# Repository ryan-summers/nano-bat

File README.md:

# NanoBat

This repository contains the hardware and software behind NanoBat, a low-cost tool designed for
engineers and hobbyists to simulate batteries in low-power designs.

## Goals
Develop an open-source PCB design and firmware solution for simulating batteries for low-power
designs with a final cost of less than $100 per unit and can accurately simulate battery capacity
over a 24 hour window with **TBD** accuracy.

## Tools
The firmware will be developed in Rust.

The PCB design will be conducted with Kicad.

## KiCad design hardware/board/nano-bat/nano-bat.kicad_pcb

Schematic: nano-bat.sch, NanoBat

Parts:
C101: 10n; C_0603_1608Metric; Part 399-7842-1-ND
C102: 0.1u; C_0603_1608Metric; Part 1276-1258-1-ND
D102: LED; LED_0805_2012Metric; Part 160-1423-1-ND
F101, F102: Polyfuse; Fuse_1812_4532Metric; Part 507-1763-1-ND
FB103: Ferrite_Bead_Small; R_0603_1608Metric; Part 587-1923-1-ND
H101, H102, H103, H104: e; MountingHole_2.2mm_M2_Pad
J101: Barrel_Jack_Switch; CUI_PJ-202B; Part CP-202B-ND
J102: USB_C_Receptacle_USB2.0; USB_C_Receptacle_GCT_USB4085; Part 2073-USB4085-GF-ACT-ND
J103: Screw_Terminal_01x02; TerminalBlock_Phoenix_PT-1,5-2-3.5-H_1x02_P3.50mm_Horizontal; Part 277-1721-ND
J104: Conn_01x02; JST_PH_S2B-PH-SM4-TB_1x02-1MP_P2.00mm_Horizontal; Part 455-1749-1-ND
Q101, Q102: Q_PMOS_GSD; SOT-23; Part FDN352APCT-ND
R101, R102: 1M; R_0603_1608Metric; Part 311-1.00MHRCT-ND
R103: 1k; R_0603_1608Metric; Part 311-1.0KGRCT-ND
R104, R105: 5.1k; R_0603_1608Metric; Part RMCF0603JT5K10CT-ND
U101: USBLC6-2SC6; SOT-23-6; Part 497-5235-1-ND

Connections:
+5V: FB103.2, Q102.3 (D)
/Coulomb Counter/Vbatt_out: J103.1, J104.1; also elsewhere on the board
/Power/Vin: Q101.2 (S), Q102.2 (S), R102.1, R103.1; also elsewhere on the board
/USB_N: U101.6; also elsewhere on the board
/USB_P: U101.4; also elsewhere on the board
GND: C101.2, C102.2, D102.1 (K), H101.1, H102.1, H103.1, H104.1, J101.2, J102.A1, J102.A12, J102.B1, J102.B12, J103.2, J104.2, Q101.1 (G), R101.2, R104.2, R105.2, U101.2; also elsewhere on the board
unnamed: C101.1, J102.S1, R101.1
unnamed: C102.1, F102.2, J102.A4, J102.A9, J102.B4, J102.B9, U101.5
unnamed: D102.2 (A), R103.2
unnamed: F101.1, Q101.3 (D)
unnamed: F101.2, J101.1
unnamed: F102.1, FB103.1
unnamed: J101.3, Q102.1 (G), R102.2
unnamed: J102.A5, R104.1
unnamed: J102.A6, J102.B6, U101.3
unnamed: J102.A7, J102.B7, U101.1
unnamed: J102.B5, R105.1

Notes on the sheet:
When the barrel jack is powered, it will override USB as the supply source and will be used as the main system rail. If the barrel-jack is not connected, USB power will be used.

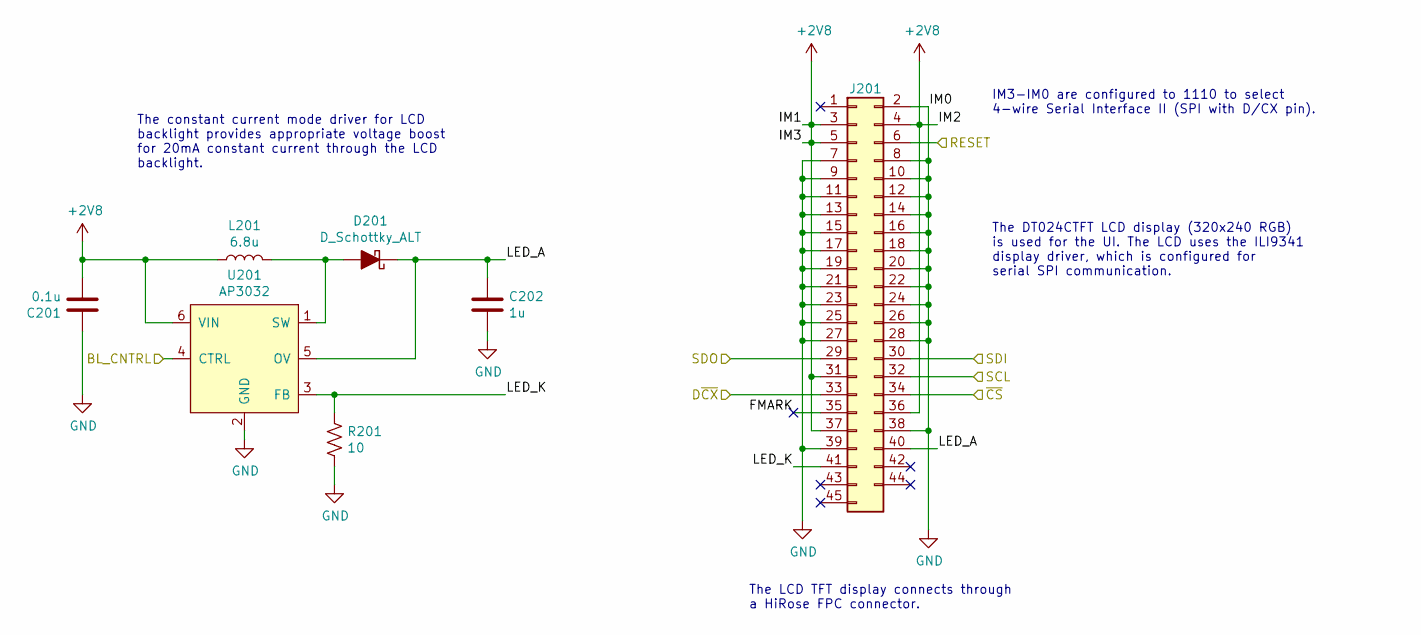
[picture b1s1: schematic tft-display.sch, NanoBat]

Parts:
C201: 0.1u; C_0603_1608Metric; Part 1276-1258-1-ND
C202: 1u; C_0603_1608Metric; Part 1276-1182-1-ND
D201: D_Schottky_ALT; D_SOD-323; Part BAT54HT1GOSCT-ND
J201: Conn_2Rows-45Pins; Hirose_FH12-45S-0.5SH_1x45-1MP_P0.50mm_Horizontal; Part HFA145CT-ND
L201: 6.8u; L_0805_2012Metric; Part 445-6761-1-ND
R201: 10; R_0603_1608Metric; Part 311-10.0HRCT-ND
U201: AP3032; SOT-23-6; Part AP3032KTR-G1DICT-ND

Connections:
+2V8: C201.2, J201.3, J201.4, J201.5, J201.31, J201.36, J201.37, L201.1, U201.6 (VIN); also elsewhere on the board
/(Opt) TFT Display/BL_CNTRL: U201.4 (CTRL); also elsewhere on the board
/(Opt) TFT Display/D~CX: J201.33; also elsewhere on the board
/(Opt) TFT Display/FMARK: J201.35
/(Opt) TFT Display/LED_A: C202.1, D201.1 (K), J201.40, U201.5 (OV)
/(Opt) TFT Display/LED_K: J201.41, R201.1, U201.3 (FB)
/(Opt) TFT Display/RESET: J201.6; also elsewhere on the board
/(Opt) TFT Display/SCL: J201.32; also elsewhere on the board
/(Opt) TFT Display/SDI: J201.30; also elsewhere on the board
/(Opt) TFT Display/SDO: J201.29; also elsewhere on the board
/Microcontroller/TFT_~CS: J201.34; also elsewhere on the board
GND: C201.1, C202.2, J201.2, J201.7, J201.8, J201.9, J201.10, J201.11, J201.12, J201.13, J201.14, J201.15, J201.16, J201.17, J201.18, J201.19, J201.20, J201.21, J201.22, J201.23, J201.24, J201.25, J201.26, J201.27, J201.28, J201.38, J201.39, R201.2, U201.2 (GND); also elsewhere on the board
unnamed: D201.2 (A), L201.2, U201.1 (SW)

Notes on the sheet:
The constant current mode driver for LCD backlight provides appropriate voltage boost for 20mA constant current through the LCD backlight.
The LCD TFT display connects through a HiRose FPC connector.
The DT024CTFT LCD display (320x240 RGB) is used for the UI. The LCD uses the ILI9341 display driver, which is configured for serial SPI communication.
IM3-IM0 are configured to 1110 to select 4-wire Serial Interface II (SPI with D/CX pin).

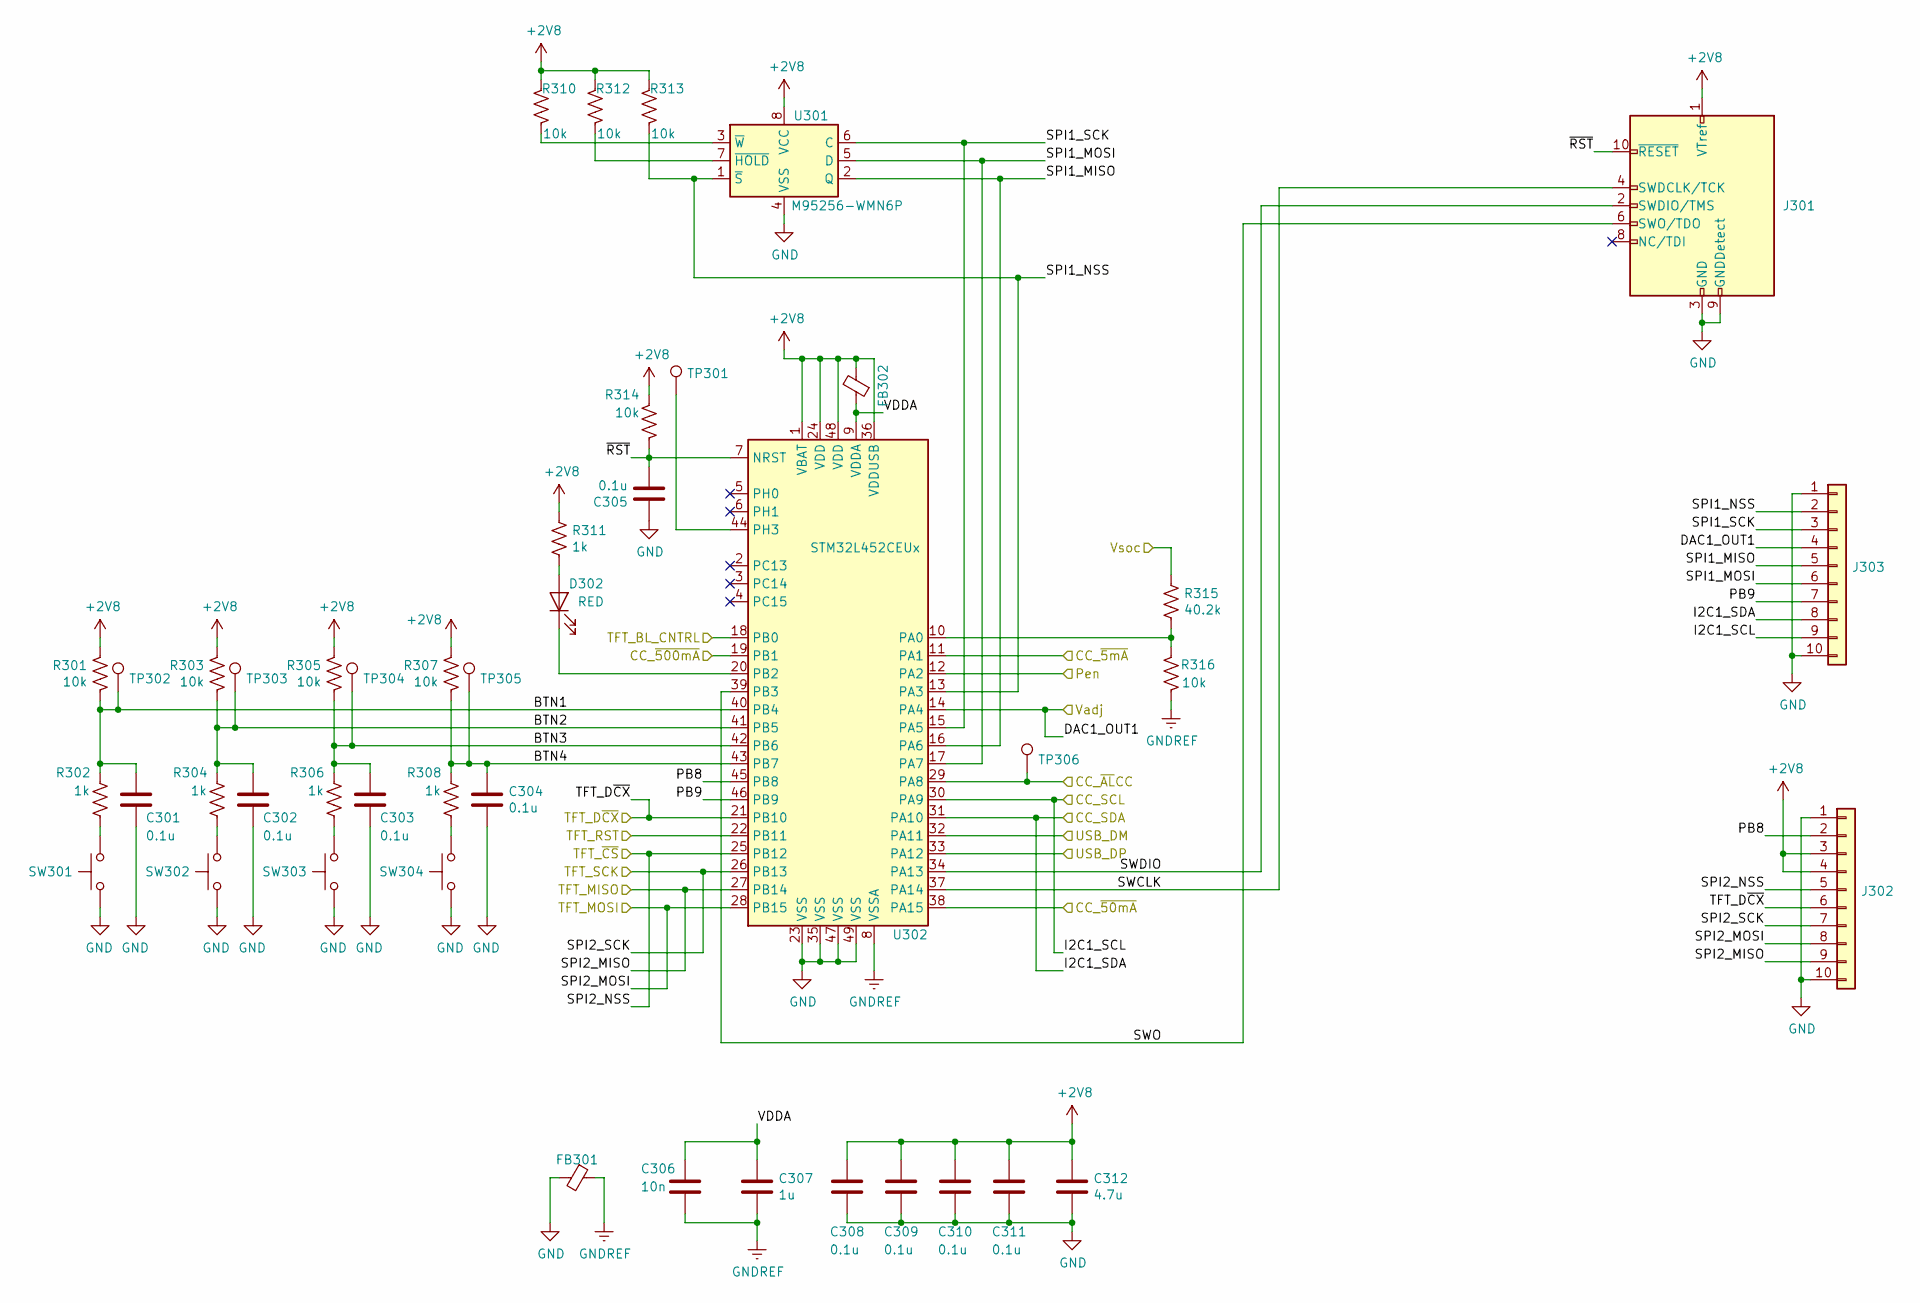
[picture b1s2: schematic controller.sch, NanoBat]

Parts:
C301, C302, C303, C304, C305, C308, C309, C310, C311: 0.1u; C_0603_1608Metric; Part 1276-1258-1-ND
C306: 10n; C_0603_1608Metric; Part 399-7842-1-ND
C307: 1u; C_0603_1608Metric; Part 1276-1182-1-ND
C312: 4.7u; C_0603_1608Metric; Part 399-3482-1-ND
D302: RED; LED_0805_2012Metric; Part 475-1278-1-ND
FB301, FB302: Ferrite_Bead_Small; R_0603_1608Metric; Part 587-1923-1-ND
J301: Conn_ARM_JTAG_SWD_10; PinHeader_2x05_P1.27mm_Vertical_SMD; Part SAM8796-ND
J302, J303: Conn_01x10; PinHeader_1x10_P2.54mm_Vertical; Part 609-3301-ND
R301, R303, R305, R307, R310, R312, R313, R314, R316: 10k; R_0603_1608Metric; Part 311-10KGRCT-ND
R302, R304, R306, R308, R311: 1k; R_0603_1608Metric; Part 311-1.0KGRCT-ND
R315: 40.2k; R_0603_1608Metric; Part RR08P40.2KDCT-ND
SW301, SW302, SW303, SW304: SW_Push; SW_B3FS-1010P; Part SW1440CT-ND
TP301: TestPoint; TestPoint_THTPad_D1.0mm_Drill0.5mm
TP302, TP303, TP304, TP305, TP306: TestPoint; TestPoint_Pad_D1.0mm
U301: M95256-WMN6P; SOIC-8_3.9x4.9mm_P1.27mm; Part 497-6357-5-ND
U302: STM32L452CEUx; QFN-48-1EP_7x7mm_P0.5mm_EP5.6x5.6mm; Part 497-17218-ND

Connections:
+2V8: C308.1, C309.1, C310.1, C311.1, C312.1, FB302.2, J301.1 (VTref), J302.3, J302.4, R301.1, R303.1, R305.1, R307.1, R310.1, R311.1, R312.1, R313.1, R314.1, U301.8 (VCC), U302.1 (VBAT), U302.24 (VDD), U302.36 (VDDUSB), U302.48 (VDD); also elsewhere on the board
/(Opt) TFT Display/BL_CNTRL: U302.18 (PB0); also elsewhere on the board
/(Opt) TFT Display/D~CX: J302.6, U302.21 (PB10); also elsewhere on the board
/(Opt) TFT Display/RESET: U302.22 (PB11); also elsewhere on the board
/(Opt) TFT Display/SCL: J302.7, U302.26 (PB13); also elsewhere on the board
/(Opt) TFT Display/SDI: J302.8, U302.28 (PB15); also elsewhere on the board
/(Opt) TFT Display/SDO: J302.9, U302.27 (PB14); also elsewhere on the board
/Coulomb Counter/Vbatt_source: R315.1; also elsewhere on the board
/Microcontroller/BTN1: C301.1, R301.2, R302.1, TP302.1, U302.40 (PB4)
/Microcontroller/BTN2: C302.1, R303.2, R304.1, TP303.1, U302.41 (PB5)
/Microcontroller/BTN3: C303.1, R305.2, R306.1, TP304.1, U302.42 (PB6)
/Microcontroller/BTN4: C304.1, R307.2, R308.1, TP305.1, U302.43 (PB7)
/Microcontroller/CC_SCL: J303.9, U302.30 (PA9); also elsewhere on the board
/Microcontroller/CC_SDA: J303.8, U302.31 (PA10); also elsewhere on the board
/Microcontroller/CC_~5mA: U302.11 (PA1); also elsewhere on the board
/Microcontroller/CC_~50mA: U302.38 (PA15); also elsewhere on the board
/Microcontroller/CC_~500mA: U302.19 (PB1); also elsewhere on the board
/Microcontroller/CC_~AL~CC: TP306.1, U302.29 (PA8); also elsewhere on the board
/Microcontroller/PB8: J302.2, U302.45 (PB8)
/Microcontroller/PB9: J303.7, U302.46 (PB9)
/Microcontroller/SPI1_MISO: J303.5, U301.2 (Q), U302.16 (PA6)
/Microcontroller/SPI1_MOSI: J303.6, U301.5 (D), U302.17 (PA7)
/Microcontroller/SPI1_NSS: J303.2, R313.2, U301.1 (~S), U302.13 (PA3)
/Microcontroller/SPI1_SCK: J303.3, U301.6 (C), U302.15 (PA5)
/Microcontroller/SWCLK: J301.4 (SWDCLK/TCK), U302.37 (PA14)
/Microcontroller/SWDIO: J301.2 (SWDIO/TMS), U302.34 (PA13)
/Microcontroller/SWO: J301.6 (SWO/TDO), U302.39 (PB3)
/Microcontroller/TFT_~CS: J302.5, U302.25 (PB12); also elsewhere on the board
/Microcontroller/VDDA: C306.1, C307.1, FB302.1, U302.9 (VDDA)
/Microcontroller/Vadj: J303.4, U302.14 (PA4); also elsewhere on the board
/Microcontroller/~RST: C305.2, J301.10 (~RESET~), R314.2, U302.7 (NRST)
/Power/En: U302.12 (PA2); also elsewhere on the board
/USB_N: U302.32 (PA11); also elsewhere on the board
/USB_P: U302.33 (PA12); also elsewhere on the board
GND: C301.2, C302.2, C303.2, C304.2, C305.1, C308.2, C309.2, C310.2, C311.2, C312.2, FB301.2, J301.3 (GND), J301.5 (GND), J301.9 (GNDDetect), J302.1, J302.10, J303.1, J303.10, SW301.2, SW302.2, SW303.2, SW304.2, U301.4 (VSS), U302.23 (VSS), U302.35 (VSS), U302.47 (VSS), U302.49 (VSS); also elsewhere on the board
GNDREF: C306.2, C307.2, FB301.1, R316.2, U302.8 (VSSA)
unnamed: D302.1 (K), U302.20 (PB2)
unnamed: D302.2 (A), R311.2
unnamed: R302.2, SW301.1
unnamed: R304.2, SW302.1
unnamed: R306.2, SW303.1
unnamed: R308.2, SW304.1
unnamed: R310.2, U301.3 (~W)
unnamed: R312.2, U301.7 (~HOLD)
unnamed: R315.2, R316.1, U302.10 (PA0)
unnamed: TP301.1, U302.44 (PH3)

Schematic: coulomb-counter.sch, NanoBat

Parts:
C401: 0.1u; C_0603_1608Metric; Part 1276-1258-1-ND
C402: 1u; C_0603_1608Metric; Part 1276-1182-1-ND
Q401, Q402, Q403: Si7615ADN; Vishay_PowerPAK_1212-8_Single; Part SI7615ADN-T1-GE3CT-ND
R401, R402: 2.2k; R_0603_1608Metric; Part P2.2KGCT-ND
R403, R407, R408, R409: 10k; R_0603_1608Metric; Part 311-10KGRCT-ND
R404: 100m; R_1206_3216Metric; Part CSR1206FKR100CT-ND
R405: 1.1; R_1206_3216Metric; Part RNCP1206FTD1R00CT-ND
R406: 10; SM6227; Part SM6227FT10R0
TP401, TP402, TP403, TP404: TestPoint; TestPoint_Pad_2.0x2.0mm; Part A106144CT-ND
U401: LTC2942; DFN-6-1EP_3x2mm_P0.5mm_EP1.65x1.35mm; Part LTC2942CDCB#TRMPBFCT-ND

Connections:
+2V8: R401.1, R402.1, R403.2; also elsewhere on the board
/Coulomb Counter/Vbatt_out: C402.1, R404.1, R405.1, R406.1, TP403.1, TP404.1, U401.6 (SENSE-); also elsewhere on the board
/Coulomb Counter/Vbatt_source: C401.2, Q401.1, Q401.2, Q401.3, Q402.1, Q402.2, Q402.3, Q403.1, Q403.2, Q403.3, R407.1, R408.1, R409.1, TP401.1, TP402.1, U401.1 (SENSE+); also elsewhere on the board
/Microcontroller/CC_SCL: R402.2, U401.3 (SCL); also elsewhere on the board
/Microcontroller/CC_SDA: R401.2, U401.4 (SDA); also elsewhere on the board
/Microcontroller/CC_~5mA: Q403.4, R409.2; also elsewhere on the board
/Microcontroller/CC_~50mA: Q402.4, R408.2; also elsewhere on the board
/Microcontroller/CC_~500mA: Q401.4, R407.2; also elsewhere on the board
/Microcontroller/CC_~AL~CC: R403.1, U401.5 (~AL~CC); also elsewhere on the board
GND: C401.1, C402.2, U401.2 (GND); also elsewhere on the board
unnamed: Q401.5, R404.2
unnamed: Q402.5, R405.2
unnamed: Q403.5, R406.2

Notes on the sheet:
Maximum Current Ranges: * 10 Ohms - 5mA * 1 Ohm - 50mA * 100mOhm - 500mA

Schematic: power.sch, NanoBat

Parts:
C501, C507, C510: 10u; C_0805_2012Metric; Part 399-3482-1-ND
C502, C503, C504: 0.1u; C_0603_1608Metric; Part 1276-1258-1-ND
C505, C506: 1u; C_0603_1608Metric; Part 1276-1182-1-ND
F501: Polyfuse; Fuse_1812_4532Metric; Part 507-1763-1-ND
L501: 4.7u; L_Taiyo-Yuden_NR-60xx; Part 587-2100-1-ND
R501: 10k; R_0603_1608Metric; Part 311-10KGRCT-ND
R502: 1.96k; R_0603_1608Metric; Part 311-1.96KHRCT-ND
R503: 9.31k; R_0603_1608Metric; Part RMCF0603FT9K31CT-ND
R504: 10k; R_0603_1608Metric; Part 311-10.0KHRCT-ND
U501: TPS562201; SOT-23-6; Part 296-44397-1-ND
U502: MCP1702; SOT-23; Part MCP1702T-3302E/CBCT-ND

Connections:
+2V8: C506.1, R501.1, U502.2 (VO); also elsewhere on the board
/Coulomb Counter/Vbatt_source: F501.1; also elsewhere on the board
/Microcontroller/Vadj: R503.2; also elsewhere on the board
/Power/En: R501.2, U501.5; also elsewhere on the board
/Power/Vin: C501.1, C502.1, C504.2, C505.1, U501.3, U502.3 (VI); also elsewhere on the board
GND: C501.2, C502.2, C504.1, C505.2, C506.2, C507.2, C510.2, R502.2, U501.1, U502.1 (GND); also elsewhere on the board
unnamed: C503.1, U501.6
unnamed: C503.2, L501.1, U501.2
unnamed: C507.1, C510.1, F501.2, L501.2, R504.2
unnamed: R502.1, R503.1, R504.1, U501.4

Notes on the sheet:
Vsoc is adjusted to bias VFB to 0.768V. Vadj is used to change the bias set-point through external analog control.
Vsoc = 5.51 - (1.0741) * Vadj

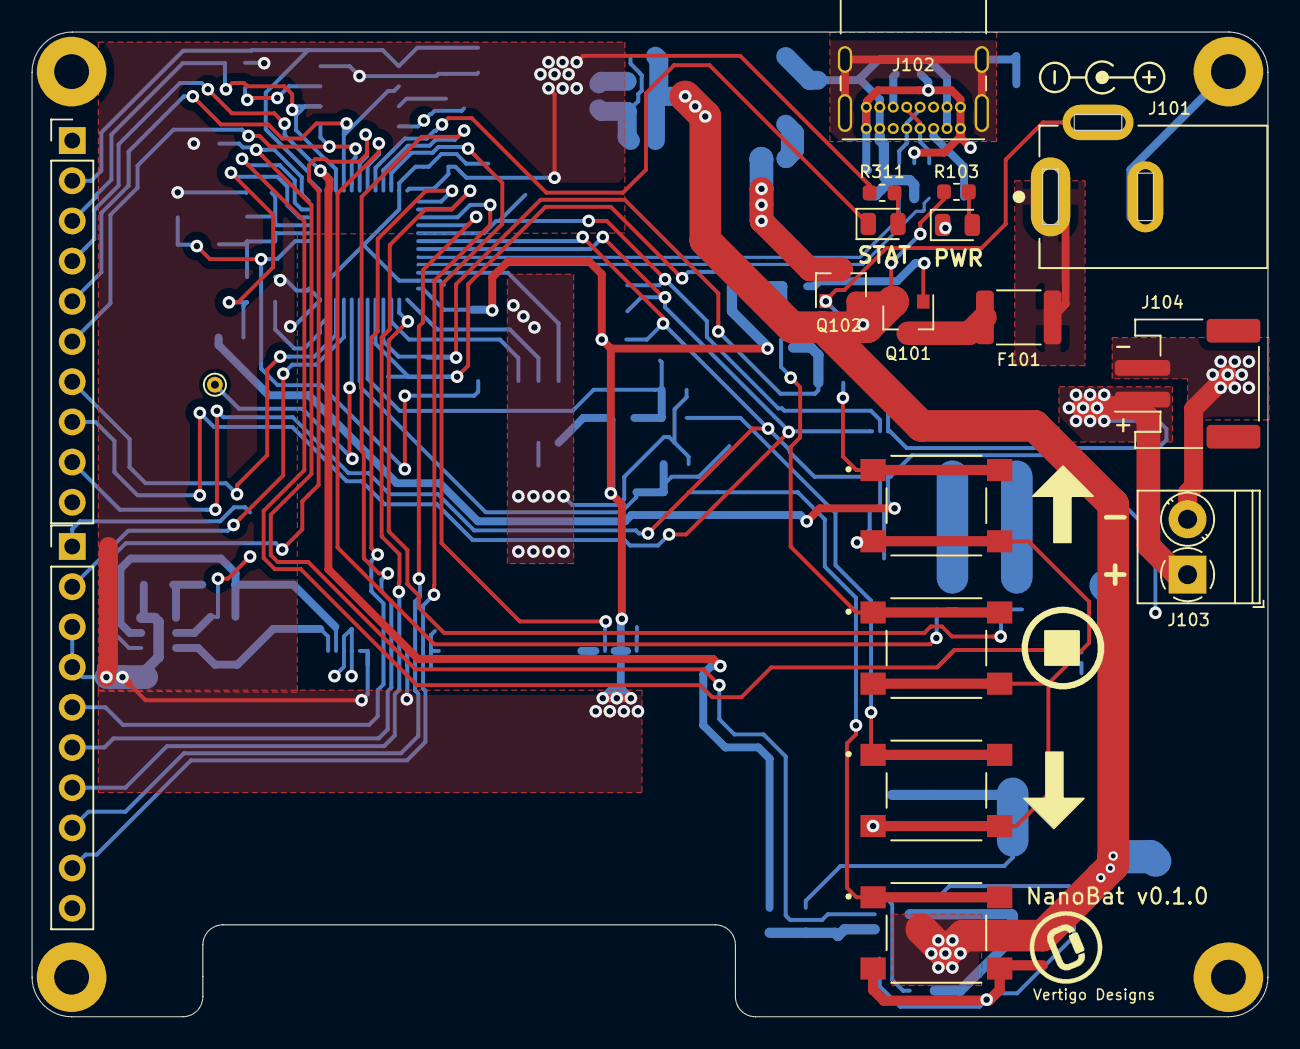
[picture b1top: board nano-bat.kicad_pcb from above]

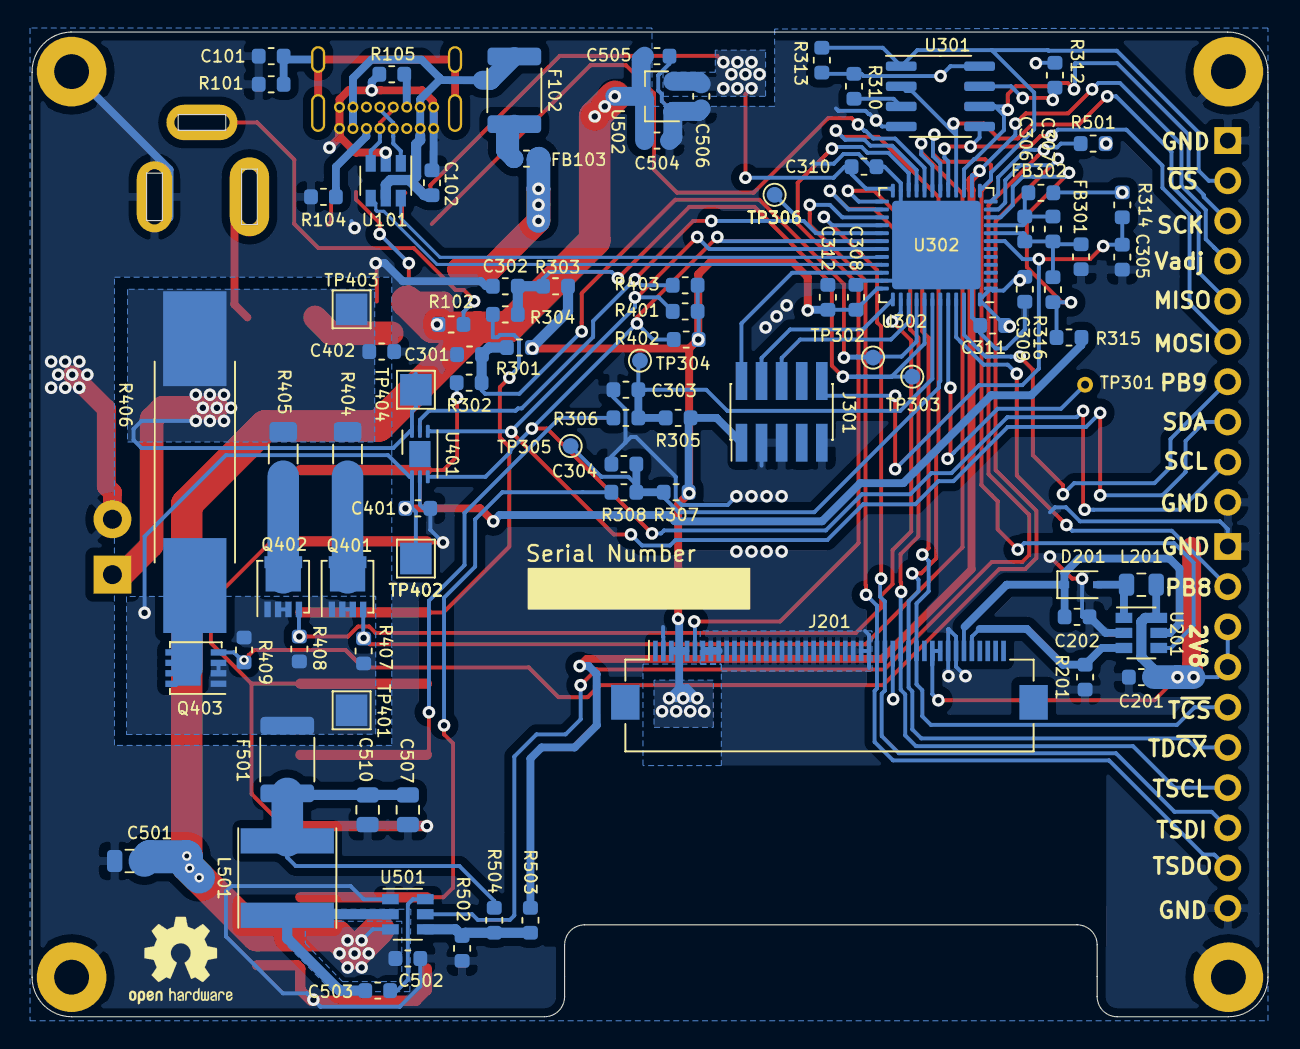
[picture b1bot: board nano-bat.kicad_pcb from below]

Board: 2 copper layers, 78.1 x 62.2 mm, 109 parts (87 on the bottom side), 70 nets.

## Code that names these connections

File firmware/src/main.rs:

#![no_std]
#![no_main]

use cortex_m;
use cortex_m_rt::entry;
use stm32l4xx_hal as hal;
use ili9341::{
    Ili9341,
    Orientation,
};
use embedded_graphics::{
    prelude::*,
    image::Image,
};
use hal::delay::Delay;
use tinybmp::Bmp;
use ltc2942;

use embedded_hal::spi::{Mode, Polarity, Phase};

use hal::prelude::*;

// pick a panicking behavior
extern crate panic_halt; // you can put a breakpoint on `rust_begin_unwind` to catch panics
// extern crate panic_abort; // requires nightly
// extern crate panic_itm; // logs messages over ITM; requires ITM support
// extern crate panic_semihosting; // logs messages to the host stderr; requires a debugger

#[entry]
fn main() -> ! {

    let cp = cortex_m::Peripherals::take().unwrap();
    let dp = hal::pac::Peripherals::take().unwrap();

    let mut flash = dp.FLASH.constrain();
    let mut rcc = dp.RCC.constrain();

    // Configure system clocks.
    let clocks = rcc.cfgr.hclk(32.mhz())
        .sysclk(64.mhz())
        .pclk2(32.mhz())
        .freeze(&mut flash.acr);

    // Configure the battery monitor.
    let mut gpioa = dp.GPIOA.split(&mut rcc.ahb2);
    let cc_alcc = gpioa.pa8.into_floating_input(&mut gpioa.moder, &mut gpioa.pupdr);
    let cc_scl = {
        let mut scl = gpioa.pa9.into_open_drain_output(&mut gpioa.moder, &mut gpioa.otyper);
        scl.internal_pull_up(&mut gpioa.pupdr, false);
        scl.into_af4(&mut gpioa.moder, &mut gpioa.afrh)
    };
    let cc_sda = {
        let mut sda = gpioa.pa10.into_open_drain_output(&mut gpioa.moder, &mut gpioa.otyper);
        sda.internal_pull_up(&mut gpioa.pupdr, false);
        sda.into_af4(&mut gpioa.moder, &mut gpioa.afrh)
    };

    let cc_i2c = hal::i2c::I2c::i2c1(
        dp.I2C1,
        (cc_scl, cc_sda),
        100.khz(),
        clocks,
        &mut rcc.apb1r1,
    );

    let mut batt_mon = ltc2942::Ltc2942::new(cc_i2c, cc_alcc).unwrap();

    batt_mon.set_sense_resistance(1f32).unwrap();

    // Constrain the reset and clock control system. We need to use this to configure the APB/AHB
    // bus for GPIOB.
    let mut gpiob = dp.GPIOB.split(&mut rcc.ahb2);
    let mut led = gpiob.pb2.into_open_drain_output(&mut gpiob.moder, &mut gpiob.otyper);
    let mut bl_control = gpiob.pb0.into_push_pull_output(&mut gpiob.moder, &mut gpiob.otyper);
    bl_control.set_high().unwrap();

    // Configure SPI for the TFT-LCD display.
    let tft_spi_sck = gpiob.pb13.into_af5(&mut gpiob.moder, &mut gpiob.afrh);
    let tft_spi_miso = gpiob.pb14.into_af5(&mut gpiob.moder, &mut gpiob.afrh);
    let tft_spi_mosi = gpiob.pb15.into_af5(&mut gpiob.moder, &mut gpiob.afrh);

    let tft_spi = hal::spi::Spi::spi2(
        dp.SPI2,
        (tft_spi_sck, tft_spi_miso, tft_spi_mosi),
        Mode{
            phase: Phase::CaptureOnFirstTransition,
            polarity: Polarity::IdleLow,
        },
        16.mhz(),
        clocks,
        &mut rcc.apb1r1,
    );

    // TODO: User a timer so that clocks are not consumed.
    let mut timer = Delay::new(cp.SYST, clocks);

    // Configure the LCD display.
    let tft_cs_n = gpiob.pb12.into_push_pull_output(&mut gpiob.moder, &mut gpiob.otyper);
    let tft_d_cx_n = gpiob.pb10.into_push_pull_output(&mut gpiob.moder, &mut gpiob.otyper);
    let tft_rst = gpiob.pb11.into_push_pull_output(&mut gpiob.moder, &mut gpiob.otyper);

    let mut display = Ili9341::new_spi(
            tft_spi,
            tft_cs_n,
            tft_d_cx_n,
            tft_rst,
            &mut timer).unwrap();

    display.set_orientation(Orientation::Portrait).unwrap();

    let bmp = Bmp::from_slice(include_bytes!("assets/vertigo-logo.bmp")).unwrap();
    Image::new(&bmp, Point::new(30, 70)).draw(&mut display).unwrap();

    loop {
        timer.delay_ms(100 as u32);
        led.set_low().unwrap();
        timer.delay_ms(100 as u32);
        led.set_high().unwrap();
    }
}

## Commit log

2019-11-19 Adding initial readme
2019-11-21 Adding initial WIP of schematic capture before upping micro size
2019-11-21 Adding larger microcontroller
2019-11-24 Adding WIP before reverting
2019-11-24 Adding complete schematic
2019-12-31 Adding first-pass revisions and annotations, part selection
2019-12-31 Adding 3D models, reorg, minor schematic fixes
2019-12-31 Removing DCM libs
2019-12-31 Adding docs to schematic
2020-01-02 Adding test points, initial board outline
2020-01-02 Updating test points, adding 3d models
2020-02-19 Adding 0.1.0 of board spin
2020-02-19 Adding cache and DCM files to version control
2020-02-19 Adding cache-lib
2020-03-06 Adding initial firmware skeleton
2020-03-06 Fixing schematic symbol sizes
2020-03-07 Adding initial enabled display and blinking LED
2020-03-07 Adding functional drawing interface
2020-03-07 Adding WIP firmware to display to screen
2020-03-07 Removing PWM work
2020-03-15 Adding WIP for battery monitor IC
